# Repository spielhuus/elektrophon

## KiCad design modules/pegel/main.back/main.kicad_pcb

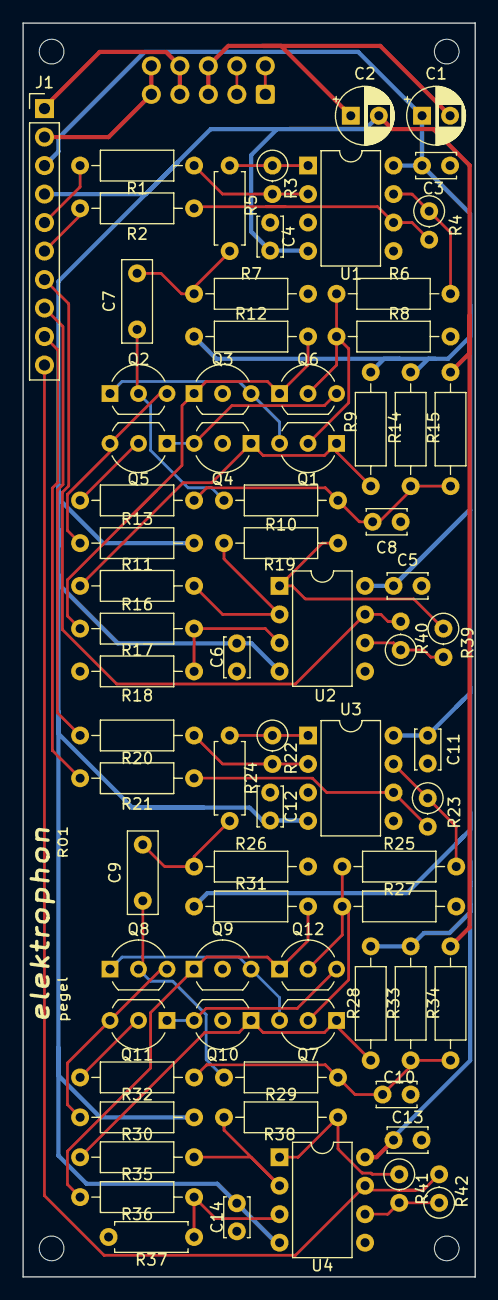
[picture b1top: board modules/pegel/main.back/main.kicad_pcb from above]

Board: 2 copper layers, 40.3 x 111.8 mm, 74 parts (1 on the bottom side), 48 nets.

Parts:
C1, C2: 10u; CP_Radial_D5.0mm_P2.50mm
C3, C4, C5, C6, C8, C10, C11, C12, C13, C14: 0.1u; C_Disc_D3.4mm_W2.1mm_P2.50mm
C7, C9: 0.22u; C_Rect_L7.2mm_W2.5mm_P5.00mm_FKS2_FKP2_MKS2_MKP2
J1: Conn_01x10_Female; PinHeader_1x10_P2.54mm_Vertical
J3: IDC Header; IDC-Header_2x05_P2.54mm_Vertical
Q1, Q2, Q3, Q4, Q5, Q6, Q7, Q8, Q9, Q10, Q11, Q12: BC550; TO-92_Inline_Wide
R1, R2, R20, R21: 100k; R_Axial_DIN0207_L6.3mm_D2.5mm_P10.16mm_Horizontal
R3, R4, R22, R23, R39, R40, R41, R42: 100k; R_Axial_DIN0207_L6.3mm_D2.5mm_P2.54mm_Vertical
R5, R24: 10k; R_Axial_DIN0207_L6.3mm_D2.5mm_P7.62mm_Horizontal
R6, R16, R17, R25, R35, R36: 10k; R_Axial_DIN0207_L6.3mm_D2.5mm_P10.16mm_Horizontal
R7, R8, R26, R27: 22; R_Axial_DIN0207_L6.3mm_D2.5mm_P10.16mm_Horizontal
R9, R11, R12, R28, R30, R31: 720; R_Axial_DIN0207_L6.3mm_D2.5mm_P10.16mm_Horizontal
R10, R13, R29, R32: 2.2k; R_Axial_DIN0207_L6.3mm_D2.5mm_P10.16mm_Horizontal
R14, R33: 3k; R_Axial_DIN0207_L6.3mm_D2.5mm_P10.16mm_Horizontal
R15, R34: 1k; R_Axial_DIN0207_L6.3mm_D2.5mm_P10.16mm_Horizontal
R18, R19, R38: 440k; R_Axial_DIN0207_L6.3mm_D2.5mm_P10.16mm_Horizontal
R37: 440k; R_Axial_DIN0207_L6.3mm_D2.5mm_P7.62mm_Horizontal
U1, U2, U3, U4: TL072; DIP-8_W7.62mm

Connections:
+5V: J1.2, J3.9, J3.10
+15V: C1.1, C3.1, C5.1, C11.1, C13.1, J1.3, R9.1, R12.1, R14.1, R28.1, R31.1, R33.1, U1.8, U2.8, U3.8, U4.8
-15V: C2.2, C4.2, C6.2, C12.2, C14.2, J1.4, R11.2, R15.2, R30.2, R34.2, U1.4, U2.4, U3.4, U4.4
/+VIN: J3.3, J3.4
/-VIN: J3.1, J3.2
DIFF1_a: Q1.1, Q4.1, R9.2, R16.1
DIFF1_b: Q7.1, Q10.1, R28.2, R35.1
DIFF2_a: Q3.1, Q6.1, R12.2, R17.1
DIFF2_b: Q9.1, Q12.1, R31.2, R36.1
GND: C1.2, C2.1, C3.2, C4.1, C5.2, C6.1, C8.1, C10.1, C11.2, C12.1, C13.2, C14.1, J1.1, J3.5, J3.6, J3.7, J3.8, Q3.2, Q4.2, Q9.2, Q10.2, R7.1, R8.1, R18.1, R26.1, R27.1, R37.1, U1.3, U1.5, U2.5, U3.3, U3.5, U4.5
IN_1a: J1.5, R1.2
IN_1b: J1.8, R20.2
IN_2a: J1.6, R2.2
IN_2b: J1.9, R21.2
unnamed: C7.1, Q2.2, R10.2
unnamed: C8.2, R10.1, R13.1, R14.2, R15.1
unnamed: C9.1, Q8.2, R29.2
unnamed: C10.2, R29.1, R32.1, R33.2, R34.1
unnamed: Q1.3, Q2.1, Q3.3
unnamed: Q2.3, Q5.3, R11.1
unnamed: Q4.3, Q5.1, Q6.3
unnamed: Q5.2, R13.2
unnamed: Q7.3, Q8.1, Q9.3
unnamed: Q10.3, Q11.1, Q12.3
unnamed: Q11.2, R32.2
unnamed: Q8.3, Q11.3, R30.1
unnamed: R1.1, R3.2, U1.2
unnamed: R2.1, R4.2, U1.6
unnamed: R3.1, R5.2, U1.1
unnamed: R4.1, R6.2, U1.7
unnamed: R16.2, R19.1, U2.2
unnamed: R17.2, R18.2, U2.3
unnamed: R19.2, R39.1, U2.1
unnamed: R20.1, R22.2, U3.2
unnamed: R21.1, R23.2, U3.6
unnamed: R22.1, R24.2, U3.1
unnamed: R23.1, R25.2, U3.7
unnamed: R35.2, R38.1, U4.2
unnamed: R36.2, R37.2, U4.3
unnamed: R38.2, R41.1, U4.1
unnamed: R39.2, R40.1, U2.6
unnamed: R41.2, R42.1, U4.6
OUT_a: J1.7, R40.2, U2.7
OUT_b: J1.10, R42.2, U4.7
Xa: C7.2, R5.1, R7.2
Xb: C9.2, R24.1, R26.2
Ya: Q1.2, Q6.2, R6.1, R8.2
Yb: Q7.2, Q12.2, R25.1, R27.2

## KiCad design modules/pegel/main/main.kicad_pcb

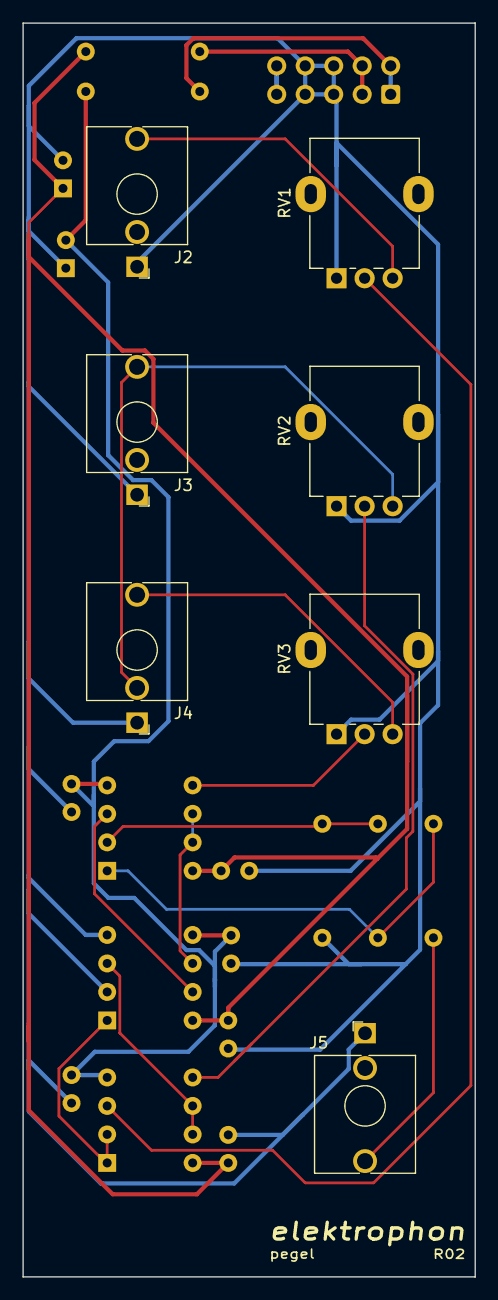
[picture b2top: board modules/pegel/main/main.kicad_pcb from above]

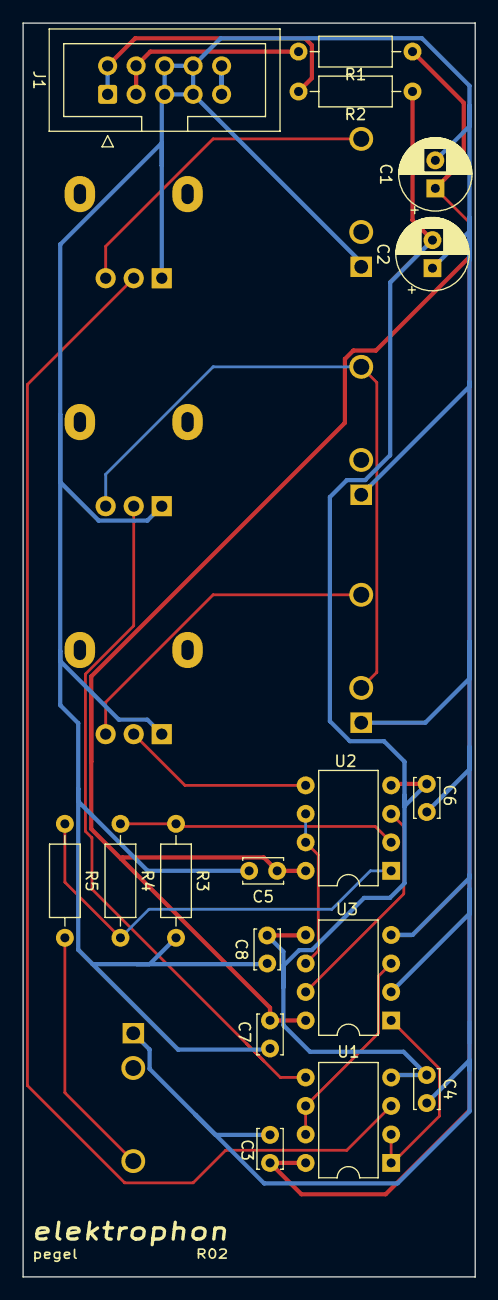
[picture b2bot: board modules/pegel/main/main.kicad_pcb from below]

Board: 2 copper layers, 40.3 x 111.8 mm, 24 parts (17 on the bottom side), 19 nets.

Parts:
C1, C2: 22u; CP_Radial_D6.3mm_P2.50mm
C3, C4, C5, C6, C7, C8: 0.1u; C_Disc_D3.4mm_W2.1mm_P2.50mm
J1: IDC Header; IDC-Header_2x05_P2.54mm_Vertical
J2: IN_X; Jack_3.5mm_WQP-PJ398SM_Vertical
J3: IN_Y; Jack_3.5mm_WQP-PJ398SM_Vertical
J4: IN_Z; Jack_3.5mm_WQP-PJ398SM_Vertical
J5: OUT; Jack_3.5mm_WQP-PJ398SM_Vertical
R1, R2: 10; R_Axial_DIN0207_L6.3mm_D2.5mm_P10.16mm_Horizontal
R3, R4: 10k; R_Axial_DIN0207_L6.3mm_D2.5mm_P10.16mm_Horizontal
R5: 1k; R_Axial_DIN0207_L6.3mm_D2.5mm_P10.16mm_Horizontal
RV1, RV2, RV3: 100k; Potentiometer_Alpha_RD901F-40-00D_Single_Vertical
U1, U2: TL072; DIP-8_W7.62mm
U3: AD633; DIP-8_W7.62mm

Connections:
+5V: J1.9, J1.10
+15V: C1.1, C3.1, C5.1, C7.1, R1.1, U1.8, U2.8, U3.8
-15V: C2.2, C4.2, C6.2, C8.2, R2.1, U1.4, U2.4, U3.5
GND: C1.2, C2.1, C3.2, C4.1, C5.2, C6.1, C7.2, C8.1, J1.5, J1.6, J1.7, J1.8, J2.S, J3.S, J4.S, J5.S, R3.2, RV1.1, RV2.1, RV3.1, U3.2, U3.4
unnamed: J2.T, RV1.3
unnamed: J3.T, J4.TN, RV2.3
unnamed: J4.T, RV3.3
unnamed: J5.T, R5.2
unnamed: R3.1, R4.2, U2.2
unnamed: R4.1, R5.1, U2.1
unnamed: RV1.2, U1.3
unnamed: RV2.2, U1.5
unnamed: RV3.2, U2.5
unnamed: U2.3, U3.7
VN: J1.1, J1.2, R2.2
VP: J1.3, J1.4, R1.2
Xa: U1.1, U1.2, U3.1
Ya: U1.6, U1.7, U3.3
Za: U2.6, U2.7, U3.6

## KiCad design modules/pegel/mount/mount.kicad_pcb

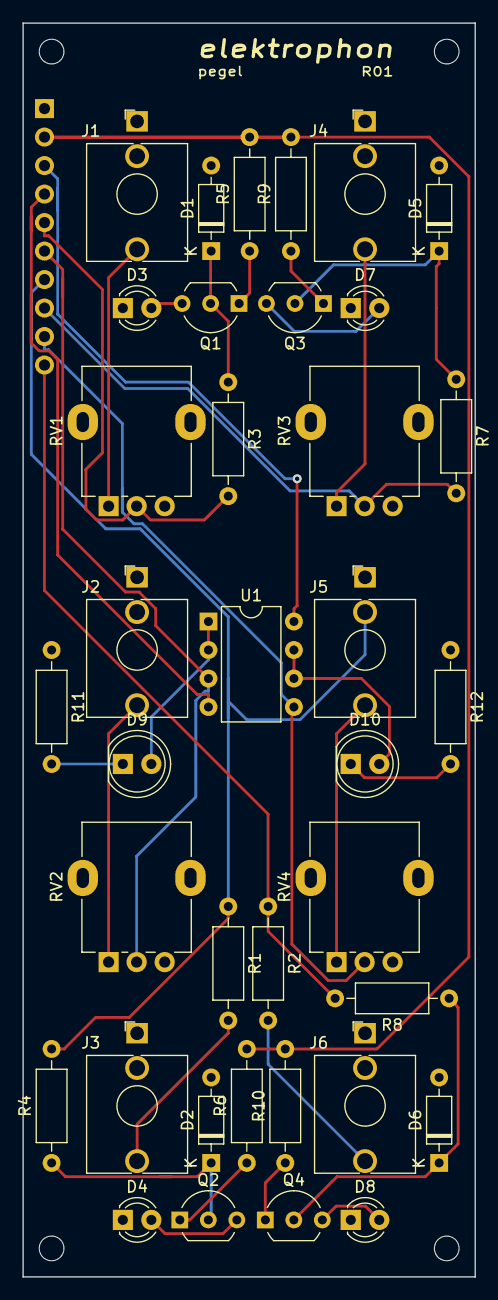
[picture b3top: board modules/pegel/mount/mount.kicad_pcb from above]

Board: 2 copper layers, 40.3 x 111.8 mm, 38 parts (1 on the bottom side), 32 nets.

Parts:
D1, D2, D5, D6: 1N4148; D_DO-35_SOD27_P7.62mm_Horizontal
D3, D4, D7, D8: WP710A10L; LED_D3.0mm
D9, D10: LED_Dual_2pin; LED_D5.0mm
J1: IN_1a; Jack_3.5mm_WQP-PJ398SM_Vertical
J2: IN_2a; Jack_3.5mm_WQP-PJ398SM_Vertical
J3: OUT_a; Jack_3.5mm_WQP-PJ398SM_Vertical
J4: IN_1b; Jack_3.5mm_WQP-PJ398SM_Vertical
J5: IN_2b; Jack_3.5mm_WQP-PJ398SM_Vertical
J6: OUT_b; Jack_3.5mm_WQP-PJ398SM_Vertical
J7: Conn_01x10_Male; PinHeader_1x10_P2.54mm_Vertical
Q1, Q2, Q3, Q4: BC550; TO-92_Inline_Wide
R1, R2: 1k; R_Axial_DIN0207_L6.3mm_D2.5mm_P10.16mm_Horizontal
R3, R4, R7, R8: 100k; R_Axial_DIN0207_L6.3mm_D2.5mm_P10.16mm_Horizontal
R5, R6, R9, R10: 5.6k; R_Axial_DIN0207_L6.3mm_D2.5mm_P10.16mm_Horizontal
R11, R12: 490; R_Axial_DIN0207_L6.3mm_D2.5mm_P10.16mm_Horizontal
RV1, RV2, RV3, RV4: 100k; Potentiometer_Alpha_RD901F-40-00D_Single_Vertical
U1: TL072; DIP-8_W7.62mm

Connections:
+5V: J7.2, R5.2, R6.2, R9.2, R10.2
+15V: J7.3, U1.8
-15V: J7.4, U1.4
GND: D1.2, D2.2, D3.1, D4.1, D5.2, D6.2, D7.1, D8.1, J1.S, J2.S, J3.S, J4.S, J5.S, J6.S, J7.1, R11.1, R12.1, RV1.3, RV2.3, RV3.3, RV4.3
IN_1a: J7.5, R3.2, RV1.2
IN_1b: J7.8, R7.2, RV3.2
IN_2a: J7.6, RV2.2, U1.3
IN_2b: J7.9, RV4.2, U1.5
unnamed: D1.1, Q1.2, R3.1
unnamed: D2.1, Q2.2, R4.1
unnamed: D3.2, Q1.3
unnamed: D4.2, Q2.3
unnamed: D5.1, Q3.2, R7.1
unnamed: D6.1, Q4.2, R8.1
unnamed: D7.2, Q3.3
unnamed: D8.2, Q4.3
unnamed: D9.1, R11.2
unnamed: D9.2, U1.1, U1.2
unnamed: D10.1, R12.2
unnamed: D10.2, U1.6, U1.7
unnamed: J1.T, RV1.1
unnamed: J2.T, RV2.1
unnamed: J3.T, R1.2
unnamed: J4.T, RV3.1
unnamed: J5.T, RV4.1
unnamed: J6.T, R2.2
unnamed: Q1.1, R5.1
unnamed: Q2.1, R6.1
unnamed: Q3.1, R9.1
unnamed: Q4.1, R10.1
OUT_a: J5.TN, J7.7, R1.1, R4.2
OUT_b: J7.10, R2.1, R8.2

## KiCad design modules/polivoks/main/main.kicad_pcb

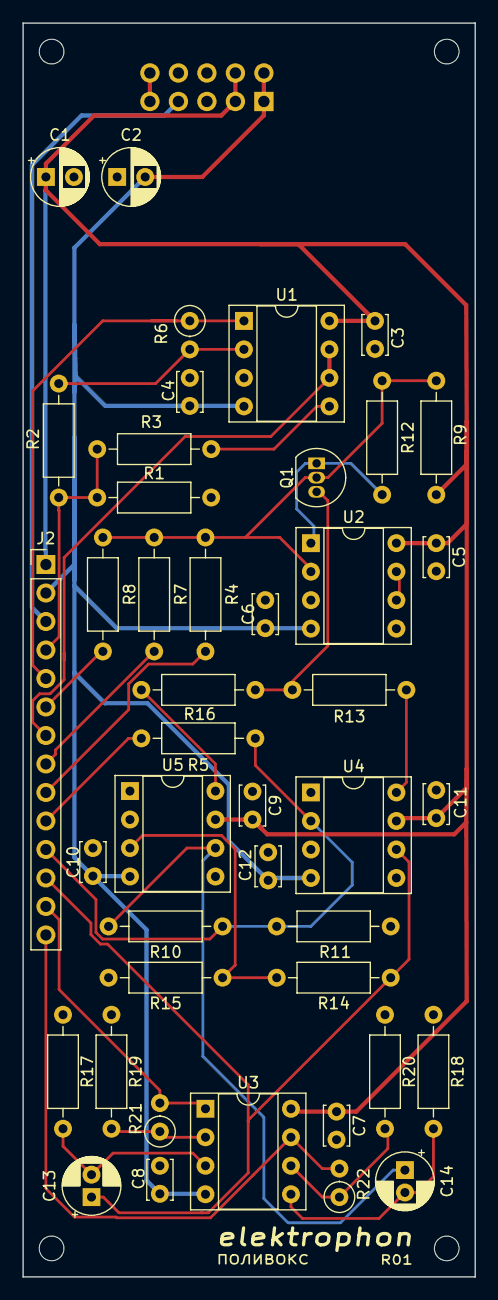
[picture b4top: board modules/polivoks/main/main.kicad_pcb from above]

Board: 2 copper layers, 40.3 x 111.8 mm, 48 parts (1 on the bottom side), 29 nets.

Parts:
C1, C2: 10u; CP_Radial_D5.0mm_P2.50mm
C3, C4, C5, C6, C7, C8, C9, C10, C11, C12: 0.1u; C_Disc_D3.4mm_W2.1mm_P2.50mm
C13, C14: 1u; CP_Radial_D5.0mm_P2.00mm
H1, H2, H3, H4: MountingHole; MountingHole_2.2mm_M2
J1: IDC Header; IDC-Header_2x05_P2.54mm_Vertical
J2: Conn_01x14_Female; PinHeader_1x14_P2.54mm_Vertical
Q1: 2N3904; TO-92_Inline
R1: 220k; R_Axial_DIN0207_L6.3mm_D2.5mm_P10.16mm_Horizontal
R2, R4, R9, R17, R18: 100k; R_Axial_DIN0207_L6.3mm_D2.5mm_P10.16mm_Horizontal
R3, R19, R20: 10k; R_Axial_DIN0207_L6.3mm_D2.5mm_P10.16mm_Horizontal
R5: 470k; R_Axial_DIN0207_L6.3mm_D2.5mm_P10.16mm_Horizontal
R6, R21, R22: 100k; R_Axial_DIN0207_L6.3mm_D2.5mm_P2.54mm_Vertical
R7: 162k; R_Axial_DIN0207_L6.3mm_D2.5mm_P10.16mm_Horizontal
R8: 120k; R_Axial_DIN0207_L6.3mm_D2.5mm_P10.16mm_Horizontal
R10, R14: 47k; R_Axial_DIN0207_L6.3mm_D2.5mm_P10.16mm_Horizontal
R11, R15: 1k; R_Axial_DIN0207_L6.3mm_D2.5mm_P10.16mm_Horizontal
R12: 3k; R_Axial_DIN0207_L6.3mm_D2.5mm_P10.16mm_Horizontal
R13, R16: 1M2; R_Axial_DIN0207_L6.3mm_D2.5mm_P10.16mm_Horizontal
U1, U2, U3: TL072; DIP-8_W7.62mm_Socket
U4, U5: LM4250; DIP-8_W7.62mm_Socket

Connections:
+5V: J1.9, J1.10
+15V: C1.1, C3.1, C5.1, C7.1, C9.1, C11.1, J1.3, J1.4, J2.1, R9.2, U1.8, U2.8, U3.8, U4.7, U5.7
-15V: C2.2, C4.2, C6.2, C8.2, C10.2, C12.2, J1.1, J1.2, J2.2, U1.4, U2.4, U3.4, U4.4, U5.4
/bp_out: J2.13, R21.2, U3.1
/cv: J2.9, R4.2
/fm_in: J2.4, R1.2, R2.2, R3.2
/fm_level_1: J2.7, U1.6, U1.7
/fm_level_2: J2.6, R8.2
/fm_level_3: J2.5, R6.1, U1.1
/freq: J2.8, R7.2
/in: J2.10, R5.2
/lp_out: J2.14, R22.2, U3.7
/res_1: J2.11, R5.1, R10.1, R11.2, U4.2
/res_2: C13.1, J2.12, R14.2, U4.6
GND: C1.2, C2.1, C3.2, C4.1, C5.2, C6.1, C7.2, C8.1, C9.2, C10.1, C11.2, C12.1, J1.5, J1.6, J1.7, J1.8, J2.3, R1.1, R11.1, R15.1, R17.1, R18.1, R19.1, R20.1, U1.3, U2.3, U2.5, U4.3, U5.2
unnamed: C13.2, R17.2, U3.3
unnamed: C14.1, R10.2, U5.6
unnamed: C14.2, R18.2, U3.5
unnamed: Q1.1, R12.1, U2.1
unnamed: Q1.2, R4.1, R7.1, R8.1, R9.1, R12.2, U2.2
unnamed: Q1.3, R13.2, R16.2
unnamed: R2.1, R6.2, U1.2
unnamed: R3.1, U1.5
unnamed: R13.1, U4.8
unnamed: R14.1, R15.2, U5.3
unnamed: R16.1, U5.8
unnamed: R19.2, R21.1, U3.2
unnamed: R20.2, R22.1, U3.6
unnamed: U2.6, U2.7

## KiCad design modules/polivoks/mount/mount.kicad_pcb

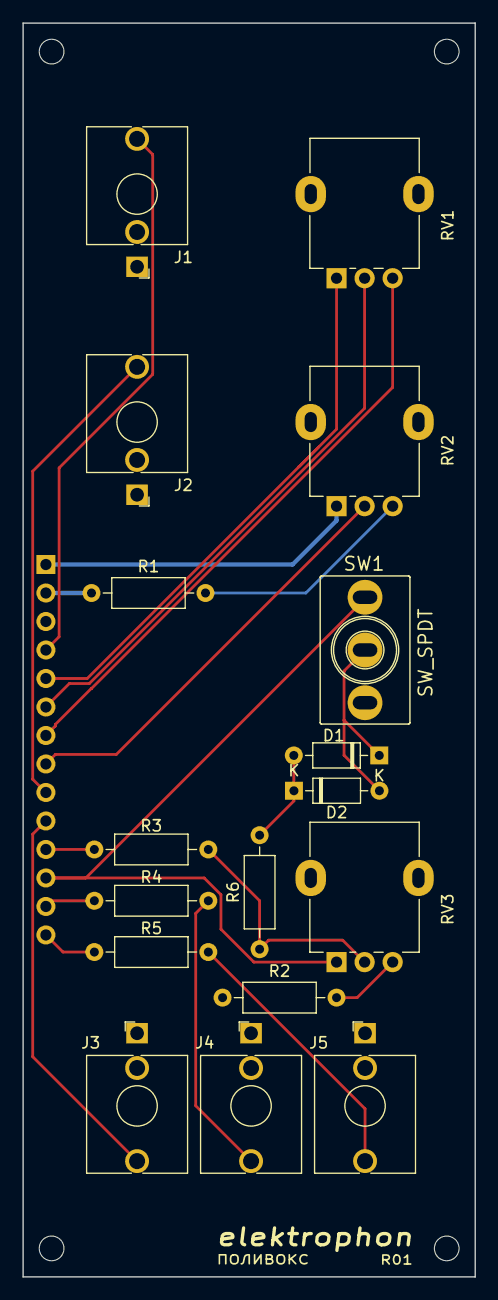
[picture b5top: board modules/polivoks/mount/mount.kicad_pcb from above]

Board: 2 copper layers, 40.3 x 111.8 mm, 22 parts (1 on the bottom side), 21 nets.

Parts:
D1, D2: 1N4148; D_DO-35_SOD27_P7.62mm_Horizontal
H1, H2, H3, H4: MountingHole; MountingHole_2.2mm_M2
J1: FM_IN; Jack_3.5mm_WQP-PJ398SM_Vertical
J2: CV_IN; Jack_3.5mm_WQP-PJ398SM_Vertical
J3: INPUT; Jack_3.5mm_WQP-PJ398SM_Vertical
J4: BP_OUT; Jack_3.5mm_WQP-PJ398SM_Vertical
J5: LP_OUT; Jack_3.5mm_WQP-PJ398SM_Vertical
J6: Conn_01x14_Male; PinHeader_1x14_P2.54mm_Vertical
R1: 47k; R_Axial_DIN0207_L6.3mm_D2.5mm_P10.16mm_Horizontal
R2: 100; R_Axial_DIN0207_L6.3mm_D2.5mm_P10.16mm_Horizontal
R3: 27k; R_Axial_DIN0207_L6.3mm_D2.5mm_P10.16mm_Horizontal
R4, R5: 1k; R_Axial_DIN0207_L6.3mm_D2.5mm_P10.16mm_Horizontal
R6: 470; R_Axial_DIN0207_L6.3mm_D2.5mm_P10.16mm_Horizontal
RV1: 47k; Potentiometer_Alpha_RD901F-40-00D_Single_Vertical
RV2, RV3: 100k; Potentiometer_Alpha_RD901F-40-00D_Single_Vertical
SW1: SW_SPDT; SPDT_KIT

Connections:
+15V: J6.1, RV2.1
-15V: J6.2, R1.1
/bp_out: J6.13, R4.1
/cv: J2.T, J6.9
/fm_in: J1.T, J6.4
/fm_level_1: J6.7, RV1.3
/fm_level_2: J6.6, RV1.2
/fm_level_3: J6.5, RV1.1
/freq: J6.8, RV2.2
/in: J3.T, J6.10
/lp_out: J6.14, R5.1
/res_1: J6.11, R3.1
/res_2: J6.12, RV3.1, SW1.1
GND: J1.S, J2.S, J3.S, J4.S, J5.S, J6.3, R2.1
unnamed: D1.1, D2.2, SW1.2
unnamed: D1.2, D2.1, R6.2
unnamed: J4.T, R4.2
unnamed: J5.T, R5.2
unnamed: R1.2, RV2.3
unnamed: R2.2, RV3.3
unnamed: R3.2, R6.1, RV3.2

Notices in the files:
modules/pegel/main.back/main.kicad_pcb:
License CC BY 4.0 - Attribution 4.0 International
